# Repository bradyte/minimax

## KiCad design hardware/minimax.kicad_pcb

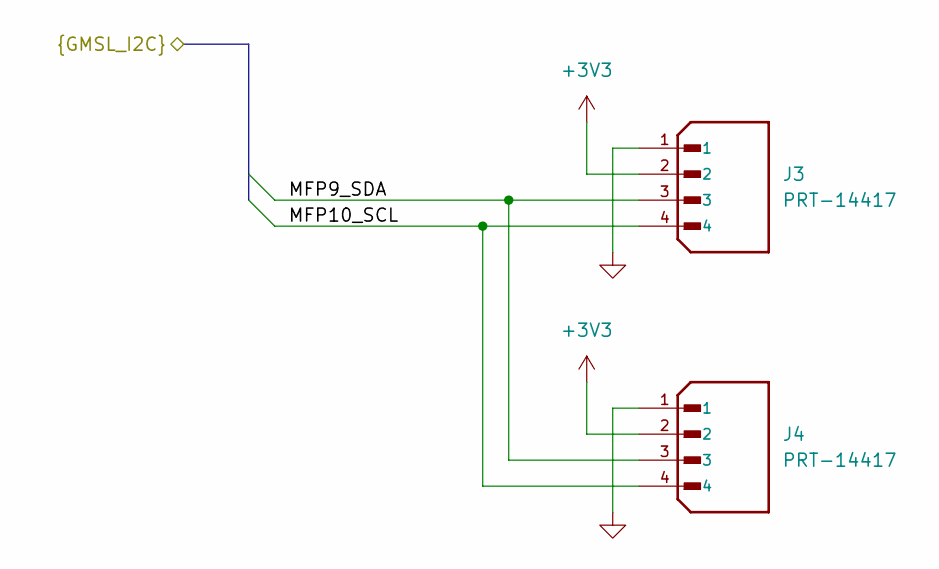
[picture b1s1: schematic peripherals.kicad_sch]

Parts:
J3, J4: PRT-14417; SPARKFUN_PRT-14417

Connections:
+3V3: J3.2, J4.2; also elsewhere on the board
/camera/MFP9_SDA: J3.3, J4.3; also elsewhere on the board
/camera/MFP10_SCL: J3.4, J4.4; also elsewhere on the board
GND: J3.1, J4.1; also elsewhere on the board

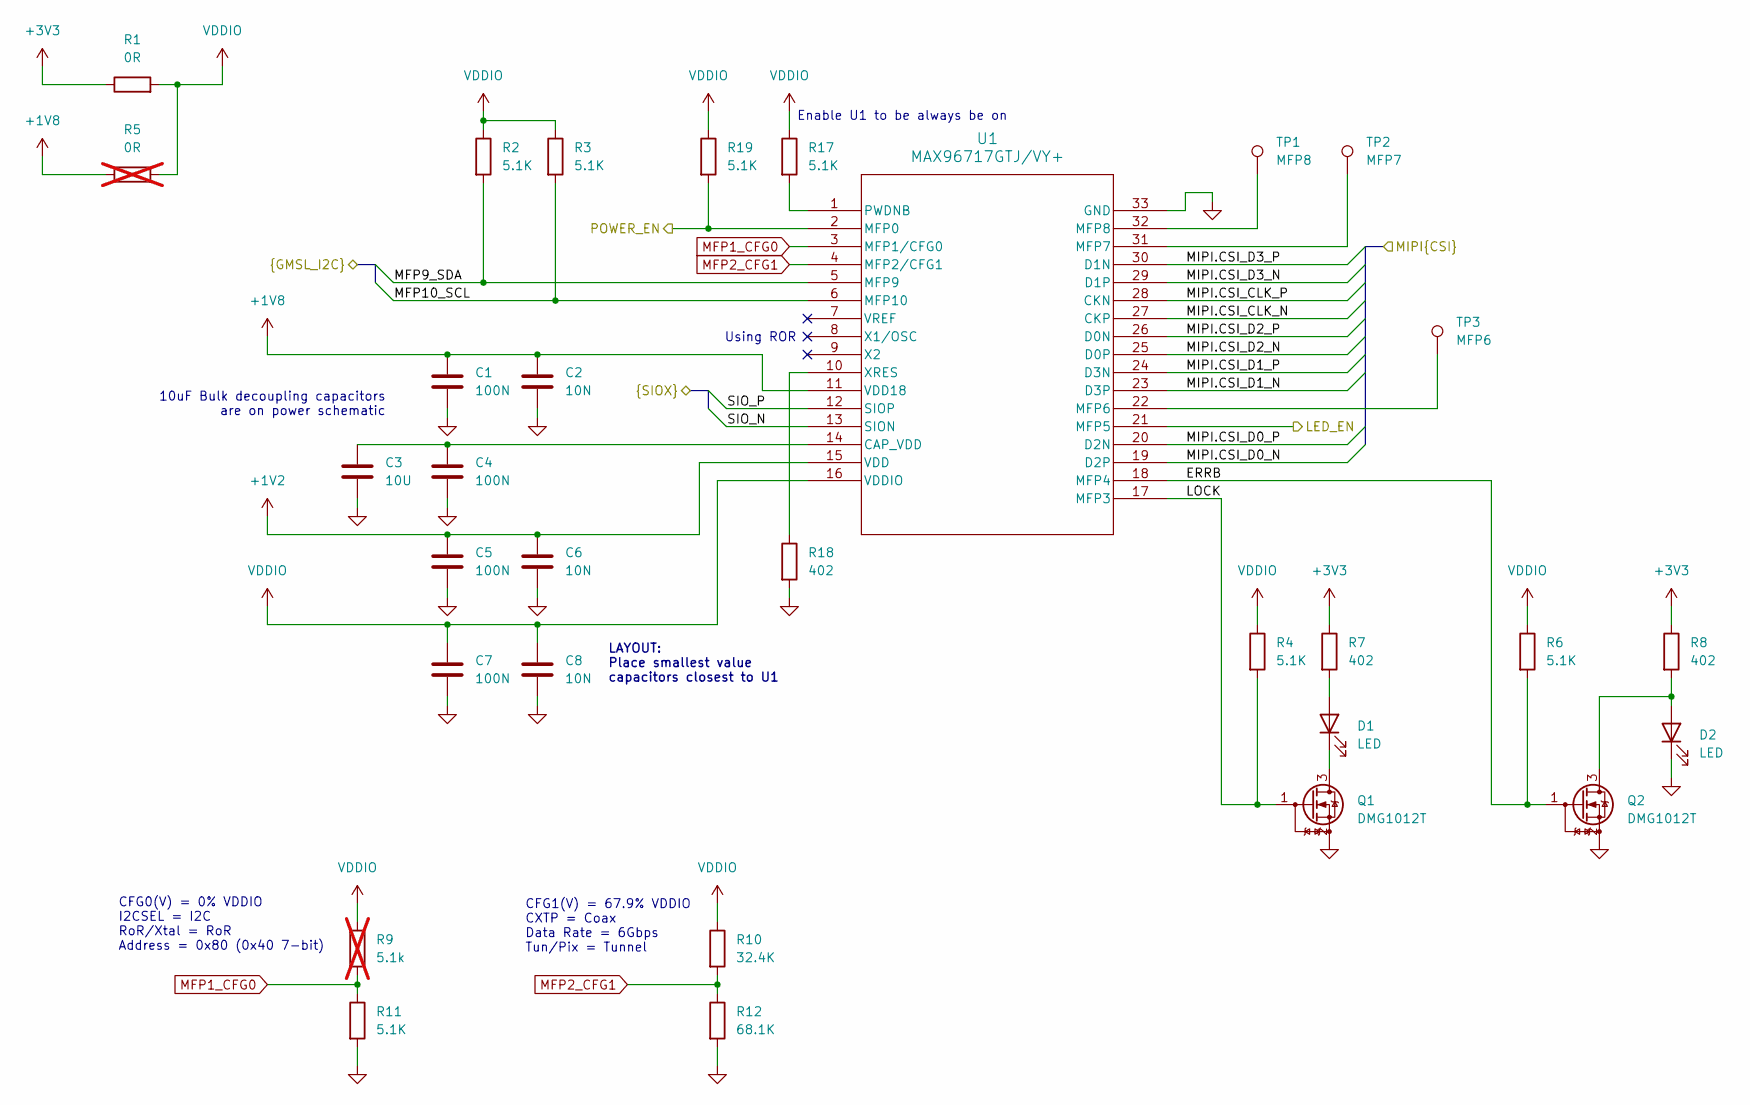
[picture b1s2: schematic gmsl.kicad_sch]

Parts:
C1, C4, C5, C7: 100N; C_0402_1005Metric
C2, C6, C8: 10N; C_0402_1005Metric
C3: 10U; C_0603_1608Metric
D1, D2: LED; LED_0603_1608Metric
Q1, Q2: DMG1012T; SOT-523
R1: 0R; R_0402_1005Metric
R2, R3, R4, R6, R11, R17, R19: 5.1K; R_0402_1005Metric
R5: 0R; R_0402_1005Metric; not fitted
R7, R8, R18: 402; R_0402_1005Metric
R9: 5.1k; R_0402_1005Metric; not fitted
R10: 32.4K; R_0402_1005Metric
R12: 68.1K; R_0402_1005Metric
TP1: MFP8; TestPoint_THTPad_D1.0mm_Drill0.5mm
TP2: MFP7; TestPoint_THTPad_D1.0mm_Drill0.5mm
TP3: MFP6; TestPoint_THTPad_D1.0mm_Drill0.5mm
U1: MAX96717GTJ/VY+; ADI_21-100156_T3255Y-8

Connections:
+1V2: C5.1, C6.1, U1.15 (VDD); also elsewhere on the board
+1V8: C1.1, C2.1, R5.1, U1.11 (VDD18); also elsewhere on the board
+3V3: R1.1, R7.1, R8.1; also elsewhere on the board
/camera/LED_EN: U1.21 (MFP5); also elsewhere on the board
/camera/MFP9_SDA: R2.2, U1.5 (MFP9); also elsewhere on the board
/camera/MFP10_SCL: R3.2, U1.6 (MFP10); also elsewhere on the board
/camera/MIPI.CSI_CLK_N: U1.27 (CKP); also elsewhere on the board
/camera/MIPI.CSI_CLK_P: U1.28 (CKN); also elsewhere on the board
/camera/MIPI.CSI_D0_N: U1.19 (D2P); also elsewhere on the board
/camera/MIPI.CSI_D0_P: U1.20 (D2N); also elsewhere on the board
/camera/MIPI.CSI_D1_N: U1.23 (D3P); also elsewhere on the board
/camera/MIPI.CSI_D1_P: U1.24 (D3N); also elsewhere on the board
/camera/MIPI.CSI_D2_N: U1.25 (D0P); also elsewhere on the board
/camera/MIPI.CSI_D2_P: U1.26 (D0N); also elsewhere on the board
/camera/MIPI.CSI_D3_N: U1.29 (D1P); also elsewhere on the board
/camera/MIPI.CSI_D3_P: U1.30 (D1N); also elsewhere on the board
/camera/POWER_EN: R19.2, U1.2 (MFP0); also elsewhere on the board
/connector/SIO_N: U1.13 (SION); also elsewhere on the board
/connector/SIO_P: U1.12 (SIOP); also elsewhere on the board
/gmsl/ERRB: Q2.1 (G), R6.2, U1.18 (MFP4)
/gmsl/LOCK: Q1.1 (G), R4.2, U1.17 (MFP3)
GND: C1.2, C2.2, C3.2, C4.2, C5.2, C6.2, C7.2, C8.2, D2.1 (K), Q1.2 (S), Q2.2 (S), R11.2, R12.2, R18.2, U1.33 (GND); also elsewhere on the board
MFP1_CFG0: R9.2, R11.1, U1.3 (MFP1/CFG0)
MFP2_CFG1: R10.2, R12.1, U1.4 (MFP2/CFG1)
unnamed: D1.2 (A), R7.2
unnamed: D1.1 (K), Q1.3 (D)
unnamed: D2.2 (A), Q2.3 (D), R8.2
unnamed: C3.1, C4.1, U1.14 (CAP_VDD)
unnamed: TP3.1, U1.22 (MFP6)
unnamed: TP2.1, U1.31 (MFP7)
unnamed: TP1.1, U1.32 (MFP8)
unnamed: R17.2, U1.1 (PWDNB)
unnamed: R18.1, U1.10 (XRES)
VDDIO: C7.1, C8.1, R1.2, R2.1, R3.1, R4.1, R5.2, R6.1, R9.1, R10.1, R17.1, R19.1, U1.16 (VDDIO)

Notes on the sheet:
LAYOUT: Place smallest value capacitors closest to U1
CFG0(V) = 0% VDDIO I2CSEL = I2C RoR/Xtal = RoR Address = 0x80 (0x40 7-bit)
10uF Bulk decoupling capacitors are on power schematic
Using ROR
CFG1(V) = 67.9% VDDIO CXTP = Coax Data Rate = 6Gbps Tun/Pix = Tunnel
Enable U1 to be always be on

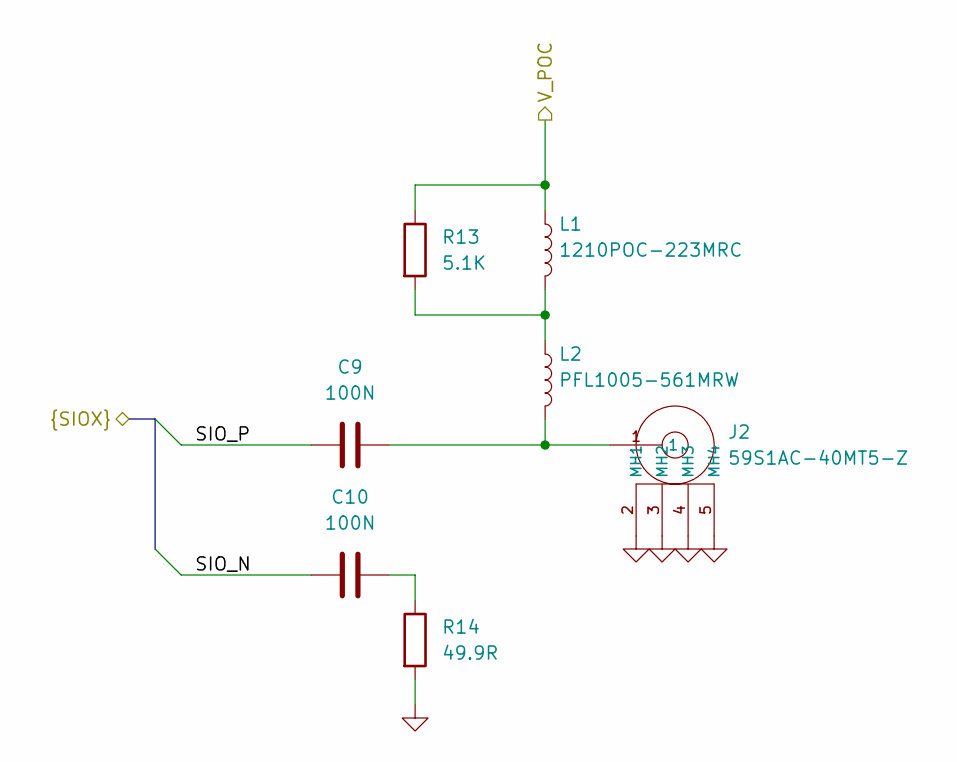
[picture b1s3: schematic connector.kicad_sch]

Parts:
C9, C10: 100N; C_0402_1005Metric
J2: 59S1AC-40MT5-Z
L1: 1210POC-223MRC; L_Coilcraft_1210POC
L2: PFL1005-561MRW; L_Coilcraft_PFL1005
R13: 5.1K; R_0402_1005Metric
R14: 49.9R; R_0402_1005Metric

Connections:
/connector/SIO_N: C10.1; also elsewhere on the board
/connector/SIO_P: C9.1; also elsewhere on the board
/connector/V_POC: L1.1, R13.1; also elsewhere on the board
GND: J2.2 (MH1), J2.3 (MH2), J2.4 (MH3), J2.5 (MH4), R14.2; also elsewhere on the board
unnamed: C9.2, J2.1, L2.2
unnamed: C10.2, R14.1
unnamed: L1.2, L2.1, R13.2

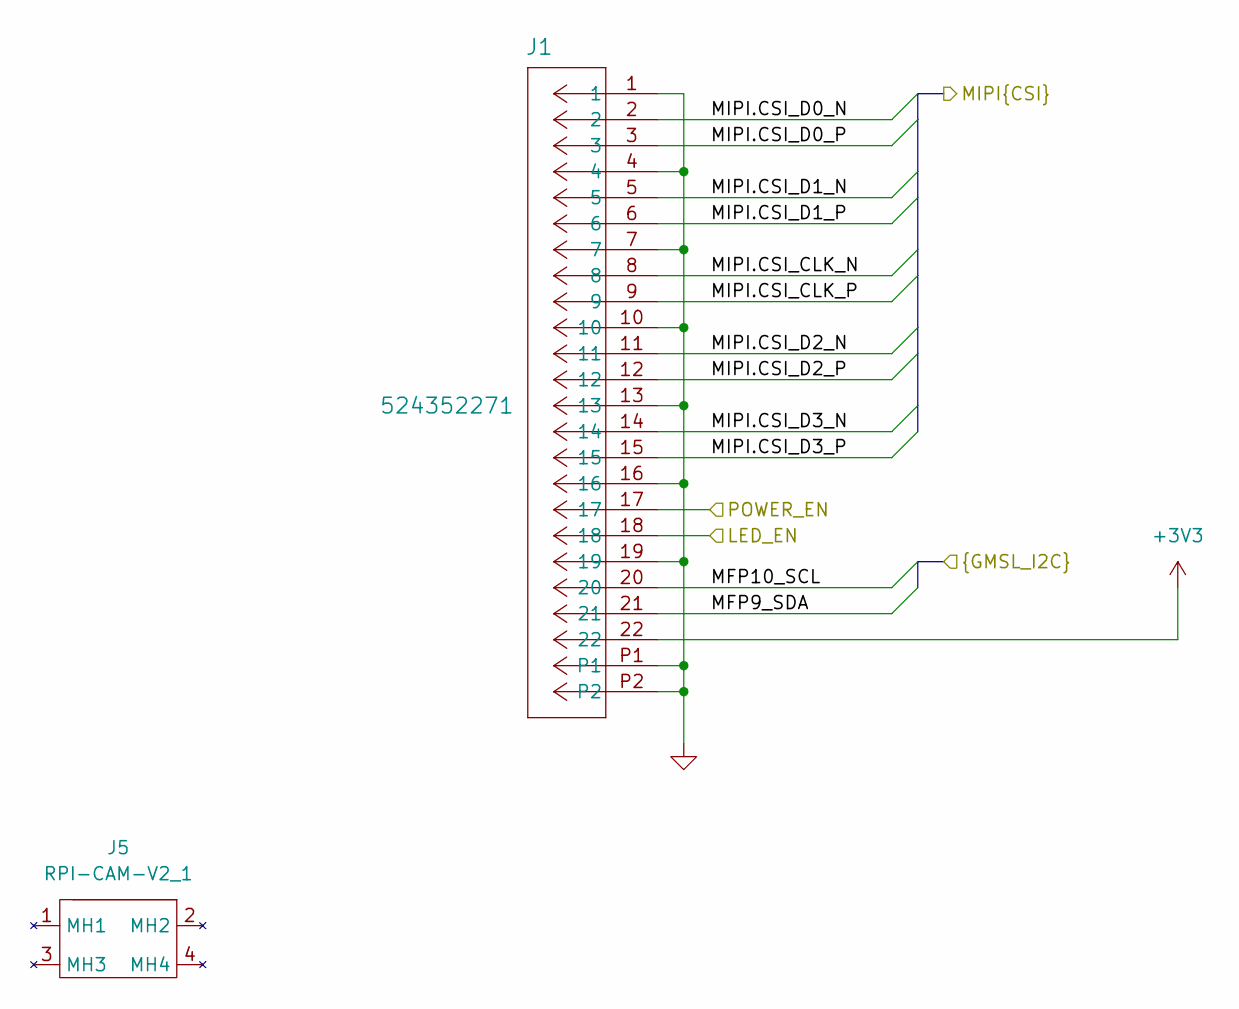
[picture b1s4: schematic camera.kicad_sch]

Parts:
J1: 524352271; CON_524352271_MOL
J5: RPI-CAM-V2_1

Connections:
+3V3: J1.22; also elsewhere on the board
/camera/LED_EN: J1.18; also elsewhere on the board
/camera/MFP9_SDA: J1.21; also elsewhere on the board
/camera/MFP10_SCL: J1.20; also elsewhere on the board
/camera/MIPI.CSI_CLK_N: J1.8; also elsewhere on the board
/camera/MIPI.CSI_CLK_P: J1.9; also elsewhere on the board
/camera/MIPI.CSI_D0_N: J1.2; also elsewhere on the board
/camera/MIPI.CSI_D0_P: J1.3; also elsewhere on the board
/camera/MIPI.CSI_D1_N: J1.5; also elsewhere on the board
/camera/MIPI.CSI_D1_P: J1.6; also elsewhere on the board
/camera/MIPI.CSI_D2_N: J1.11; also elsewhere on the board
/camera/MIPI.CSI_D2_P: J1.12; also elsewhere on the board
/camera/MIPI.CSI_D3_N: J1.14; also elsewhere on the board
/camera/MIPI.CSI_D3_P: J1.15; also elsewhere on the board
/camera/POWER_EN: J1.17; also elsewhere on the board
GND: J1.1, J1.4, J1.7, J1.10, J1.13, J1.16, J1.19, J1.P1, J1.P2; also elsewhere on the board

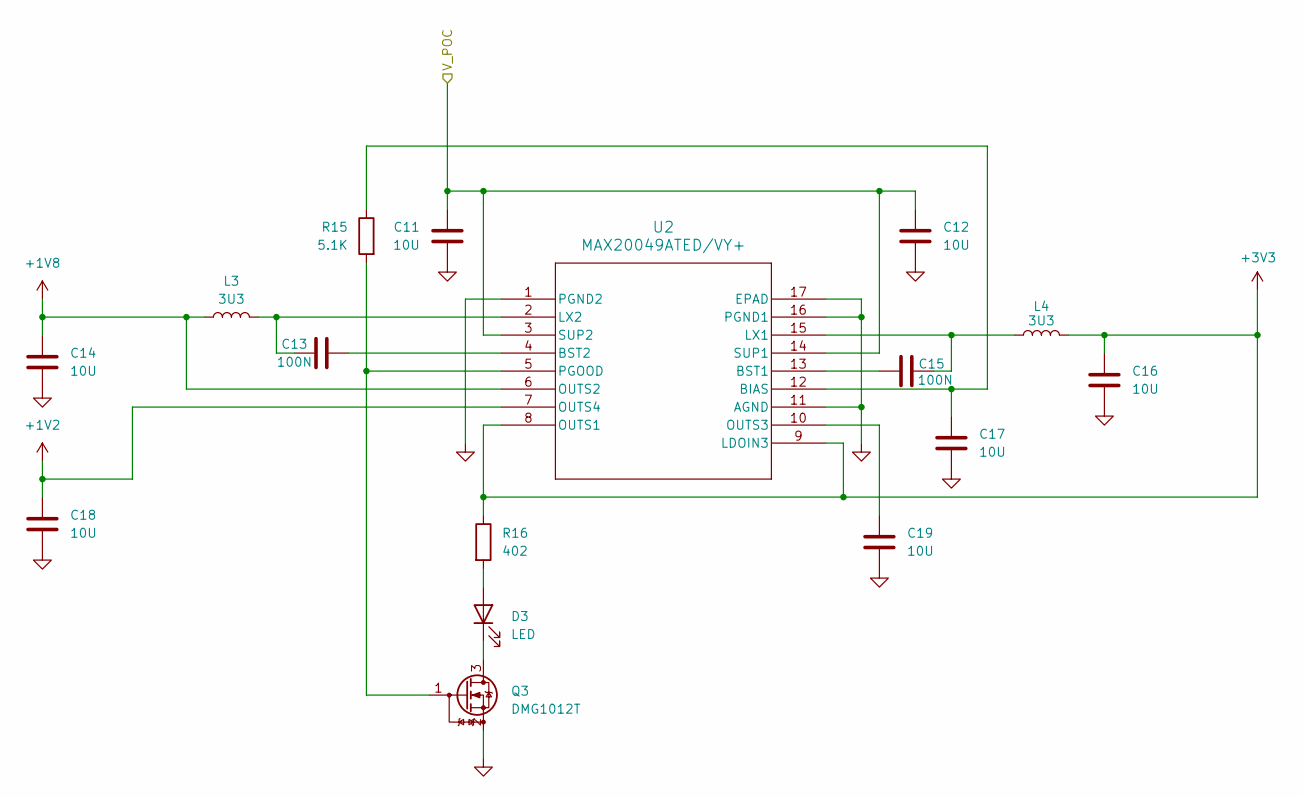
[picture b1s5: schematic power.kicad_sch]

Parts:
C11, C12, C14, C16, C17, C18, C19: 10U; C_0603_1608Metric
C13, C15: 100N; C_0402_1005Metric
D3: LED; LED_0603_1608Metric
L3, L4: 3U3; IND_TFM252012ALMA_TDK
Q3: DMG1012T; SOT-523
R15: 5.1K; R_0402_1005Metric
R16: 402; R_0402_1005Metric
U2: MAX20049ATED/VY+; 21-100150D_T1633Y&plus_5C_MXM

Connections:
+1V2: C18.1, U2.7 (OUTS4); also elsewhere on the board
+1V8: C14.1, L3.1, U2.6 (OUTS2); also elsewhere on the board
+3V3: C16.1, L4.1, R16.1, U2.8 (OUTS1), U2.9 (LDOIN3); also elsewhere on the board
/connector/V_POC: C11.1, C12.1, U2.3 (SUP2), U2.14 (SUP1); also elsewhere on the board
GND: C11.2, C12.2, C14.2, C16.2, C17.2, C18.2, C19.2, Q3.2 (S), U2.1 (PGND2), U2.11 (AGND), U2.16 (PGND1), U2.17 (EPAD); also elsewhere on the board
unnamed: D3.2 (A), R16.2
unnamed: D3.1 (K), Q3.3 (D)
unnamed: Q3.1 (G), R15.2, U2.5 (PGOOD)
unnamed: C17.1, R15.1, U2.12 (BIAS)
unnamed: C15.1, U2.13 (BST1)
unnamed: C13.2, U2.4 (BST2)
unnamed: C15.2, L4.2, U2.15 (LX1)
unnamed: C13.1, L3.2, U2.2 (LX2)
unnamed: C19.1, U2.10 (OUTS3)

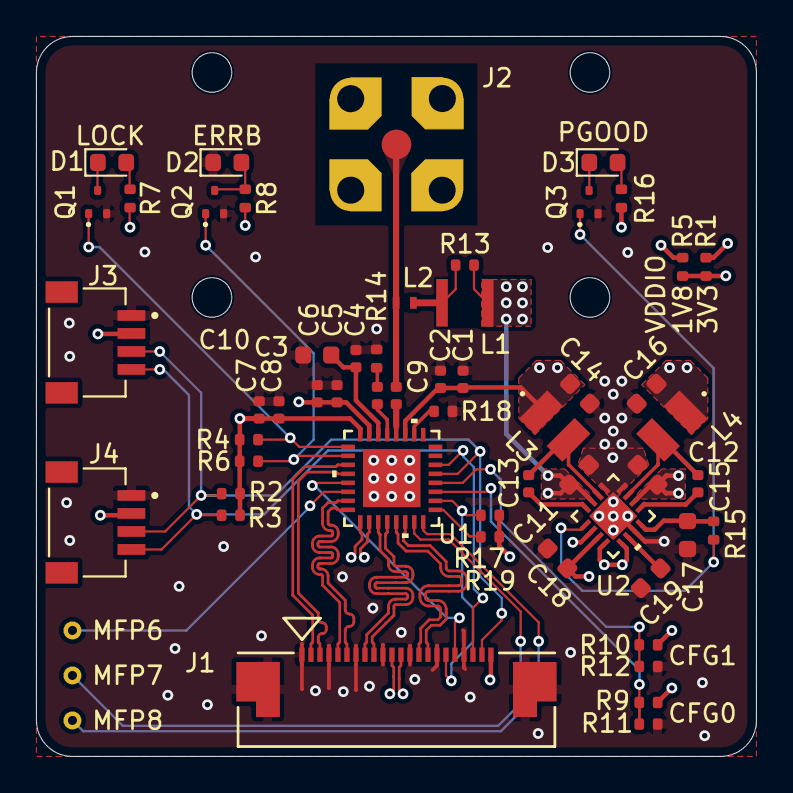
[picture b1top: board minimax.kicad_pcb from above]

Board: 4 copper layers, 40.0 x 40.0 mm, 58 parts (0 on the bottom side), 47 nets.

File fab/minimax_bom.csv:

'Value','Reference','Footprint','DNP'
'100N','C1,C4,C5,C7,C9,C10,C13,C15','Capacitor_SMD:C_0402_1005Metric',''
'10N','C2,C6,C8','Capacitor_SMD:C_0402_1005Metric',''
'10U','C3,C11,C12,C14,C16,C17,C18,C19','Capacitor_SMD:C_0603_1608Metric',''
'LED','D1,D2,D3','LED_SMD:LED_0603_1608Metric',''
'524352271','J1','user:CON_524352271_MOL',''
'59S1AC-40MT5-Z','J2','user:59S1AC-40MT5-Z',''
'PRT-14417','J3,J4','user:SPARKFUN_PRT-14417',''
'RPI-CAM-V2_1','J5','user:RPI-CAM-V2_1',''
'1210POC-223MRC','L1','user:L_Coilcraft_1210POC',''
'PFL1005-561MRW','L2','user:L_Coilcraft_PFL1005',''
'3U3','L3,L4','user:IND_TFM252012ALMA_TDK',''
'DMG1012T','Q1,Q2,Q3','Package_TO_SOT_SMD:SOT-523',''
'0R','R1','Resistor_SMD:R_0402_1005Metric',''
'5.1K','R2,R3,R4,R6,R11,R13,R15,R17,R19','Resistor_SMD:R_0402_1005Metric',''
'402','R7,R8,R16,R18','Resistor_SMD:R_0402_1005Metric',''
'32.4K','R10','Resistor_SMD:R_0402_1005Metric',''
'68.1K','R12','Resistor_SMD:R_0402_1005Metric',''
'49.9R','R14','Resistor_SMD:R_0402_1005Metric',''
'MFP8','TP1','TestPoint:TestPoint_THTPad_D1.0mm_Drill0.5mm',''
'MFP7','TP2','TestPoint:TestPoint_THTPad_D1.0mm_Drill0.5mm',''
'MFP6','TP3','TestPoint:TestPoint_THTPad_D1.0mm_Drill0.5mm',''
'MAX96717GTJ/VY+','U1','user:ADI_21-100156_T3255Y-8',''
'MAX20049ATED/VY+','U2','user:21-100150D_T1633Y&plus_5C_MXM',''

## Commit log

2024-09-18 initial upload
2024-09-19 mipi interface land swapping
2024-09-23 cleaned schematics and moving to rpi v2 camera form factor
2024-09-24 finished rough pass on max96717, need cfgs. added notes to imx219 inck tolerance.
2024-09-24 Removed DF37 connector
2024-09-24 added 22-pin 524352271, need to change fakra to smt
2024-09-24 cleaned up serializer with comments and project hierarchy
2024-09-24 cleaned up schematics
2024-09-25 started power, added smt fakra
2024-09-26 finished schematic, changed to 4 layer board
2024-10-04 layout planning and decided to use bottom layer for components
2024-10-04 cleaned up power supply and started minor power plane routing
2024-10-05 more serializer layout, waiting to do stackup analysis
2024-10-07 clean up
2024-10-08 added LED circuits and test points on extra MFPs
2024-10-08 cleaned up fakra footprint
2024-10-11 pics
2024-11-26 general layout changes
2024-12-03 finished schematics and layout, need final aesthetic touches
2024-12-10 submitted for board fab
2025-01-07 fixed LED logic and added pullup on the camera enable
2025-01-08 minor layout optimizations
2025-01-10 added schematic pdf
2025-03-13 prepping for fab
